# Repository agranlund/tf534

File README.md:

# TerribleFire   [![Badge License]][License]

*Atari Accelerator Card Firmware.*

<br>

## Supported Cards

<kbd>  TF530  </kbd>  <kbd>  TF534  </kbd>

<br>
<br>

## Note

By default the **TF534** doesn't work under  `25Mhz` .

With this firmware, it can work from  `25Mhz`  up to <br>
`50Mhz` , thou it is optimized for  `33Mhz`  &  `50Mhz` .

<br>
<br>

## BOM

*Where this* ***BOM*** *differs from the schematic use the* ***BOM*** *value.*

<br>

|       Part       |       Value       |         Device          |        Package         |            Description            |
|:----------------:|:-----------------:|:-----------------------:|:----------------------:|:---------------------------------:|
| `C1 - C15`       | `10uF`            | `CAP_1206_X7R`          | `1206`                 |  Ceramic Capacitors               |
| `C16 + C17`      | `0.1uF`           | `CAP_0603_X7R`          | `0603`                 | `CAP-00810`                       |
| `C18`            | `0.1uF`           | `CAP_1206_X7R`          | `1206`                 |  Ceramic Capacitors               |
| `C19`            | `0.1uF`           | `CAP_0603_X7R`          | `0603`                 |                                   |
| `C20`            | `0.1uF`           | `CAP_0603_X7R`          | `0603`                 | `CAP-00810`                       |
| `C21 - C30`      | `0.1uF`           | `CAP_0603_X7R`          | `0603`                 |                                   |
| `C31`            | `10uF`            | `CAP_1206_X7R`          | `1206`                 |  Ceramic Capacitors               |
| `IC1`            | `MC68030RC`       | `68030`                 | `MPGA128`              | `MOTOROLA`                        |
| `IC2`            | `MC68881FN-SOC`   | `68882`                 | `PLCC68-S`             | `unknown`                         |
| `IC3`            | `LM1117-3.3`      | `V_REG_LM1117SOT223`    | `SOT223`               | Voltage Regulator `LM1117`        |
| `IC4 - IC5`      | `74LVC1G17DBV`    | `74LVC1G17DBV`          | `SOT23-5`              |  Single Schmitt-Trigger Buffer    |
| `IC6 - IC9`      | `AS6C800855ZIN`   | `AS6C800855ZIN`         | `TSOP44-II`            |                                   |
| `IC10`           | `74AC16245`       | `74AC16245`             | `SSOP48DL`             | `16-bit` \| `3-state` \|BUS Transceiver |
| `IDECONNECTOR`   | `87758-4416`      | `87758-4416`            | `87758-4416`           | `44 Pin` \| `2mm` \| Dual Row HDR |
| `INT2`           | `PINHD-1X1`       | `1X01`                  | `PIN HEADER`           |                                   |
| `JP1`            | `CLOCKSEL`        | `JUMPER-3PTH`           | `1X03`                 |                                   |
| `JP2`            | `Z2ROM`           | `JUMPER-2PTH`           | `1X02`                 |  Jumper                           |
| `JP3`            | `MMUDIS`          | `JUMPER-2PTH`           | `1X02`                 |  Jumper                           |
| `JP4`            | `ROMEN`           | `JUMPER-2PTH`           | `1X02`                 |  Jumper                           |
| `JP5`            | `CDIS`            | `JUMPER-2PTH`           | `1X02`                 |  Jumper                           |
| `JTAG`           | `JTAG`            | `HEADER-1X6`            | `0.1 header x 6`       |  Pin Header                       |
| `OSCCPU`         | `CPUMHZ`          | `OSCILLATOR`            | `OSC_7X5MM`            |  Oscillators                      |
| `PWR1`           | `EXT5V`           | `JUMPER-2PTH`           | `1X02`                 |  Jumper                           |
| `R1 + R2`        | `2K2`             | `0.05OHM-1/5W-1%(0603)` | `0603`                 | `RES-12535`                       |
| `R3`             | `47K`             | `RESISTOR1206`          | `1206`                 |  Resistors                        |
| `RN1 - RN3`      | `CAY16-222J4LF`   | `CAY16-222J4LF`         | `RESCAXE80P320X160-8N` | Res Thick Film Array `2.2KΩ`      |
| `SPIPORT`        | `SPI PORT`        | `PINHD-2X6`             | `2X06`                 |  Pin Header                       |
| `SPI_INT`        | `NONE`            | `PINHD-1X1`             | `1X01`                 |  Pin Header                       |
| `U1`             | `3.3V SPI Flash`  | `SST26VF016B`           | `SO08`                 | `32M` Serial Flash Memory         |
| `X1`             | `MC68000`         | `MC68000P`              | `DIL64`                | `68xxx` Processor                 |
| `XC9572XL(BUS)`  | `XC9572XL-VQ64`   | `XC9572XL-VQ64`         | `VQ64`                 |                                   |
| `XC95144XL(RAM)` | `XC95144XL-TQ100` | `XC95144XL-TQ100`       | `TQFP100`              |                                   |

<br>

<!----------------------------------------------------------------------------->

[Badge License]: https://img.shields.io/badge/License-GPL2-015d93.svg?style=for-the-badge&labelColor=blue

[License]: LICENSE

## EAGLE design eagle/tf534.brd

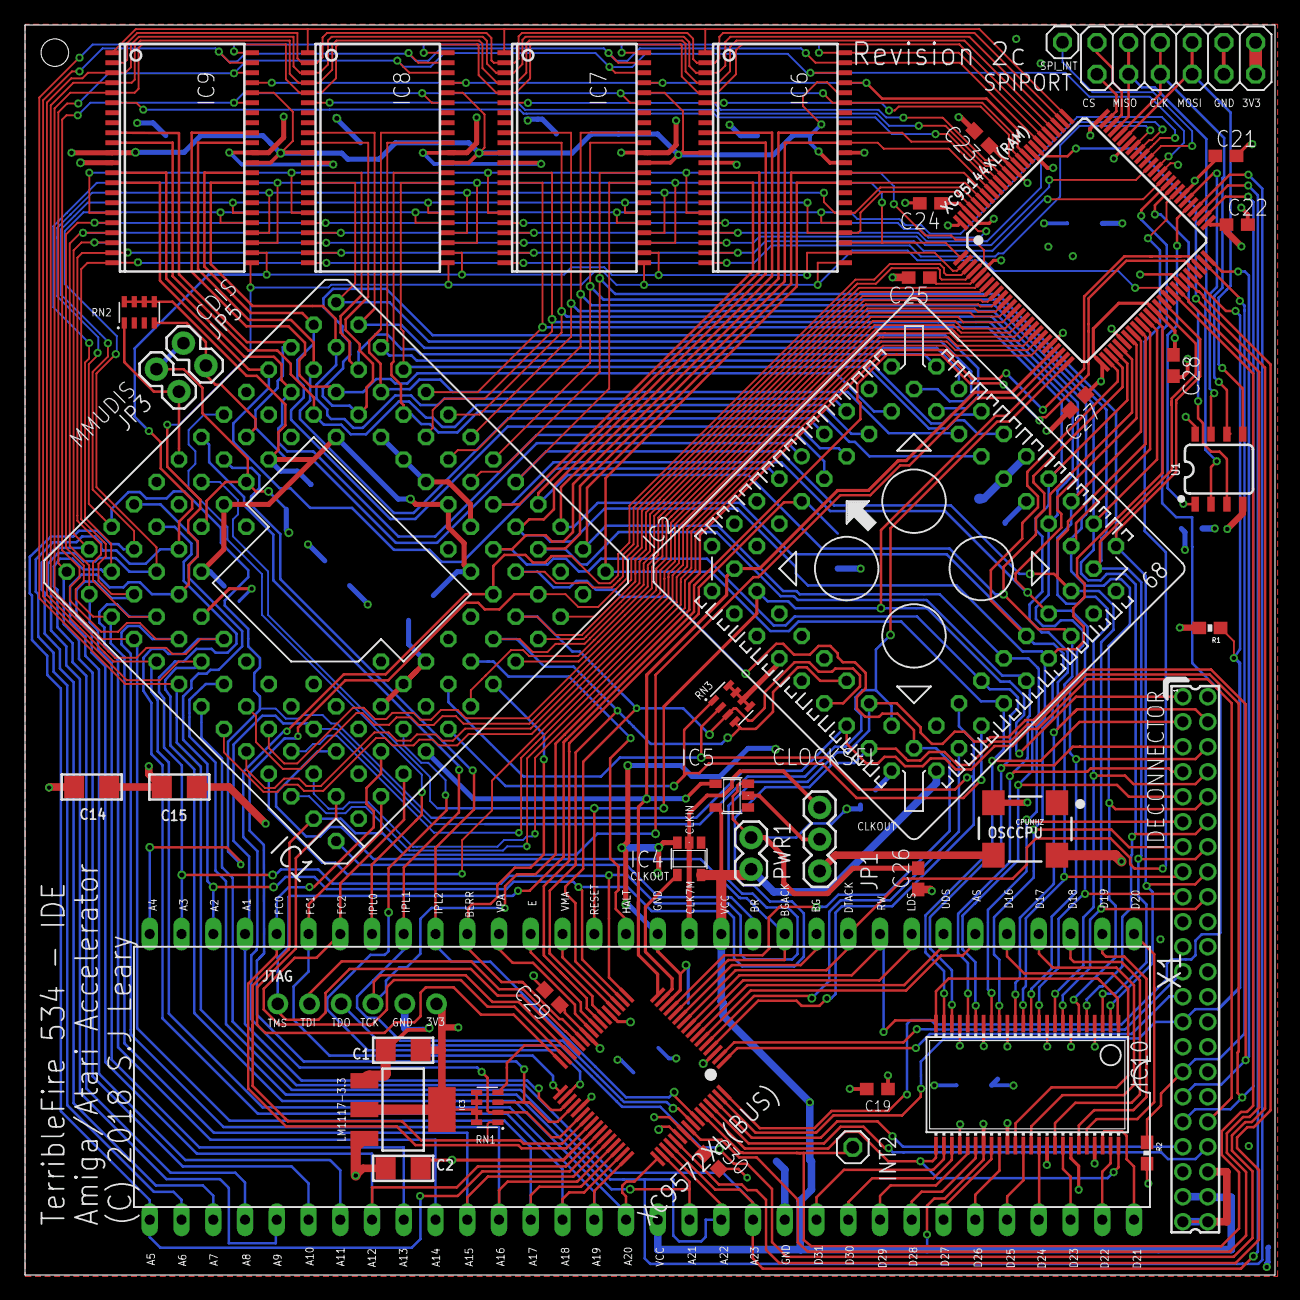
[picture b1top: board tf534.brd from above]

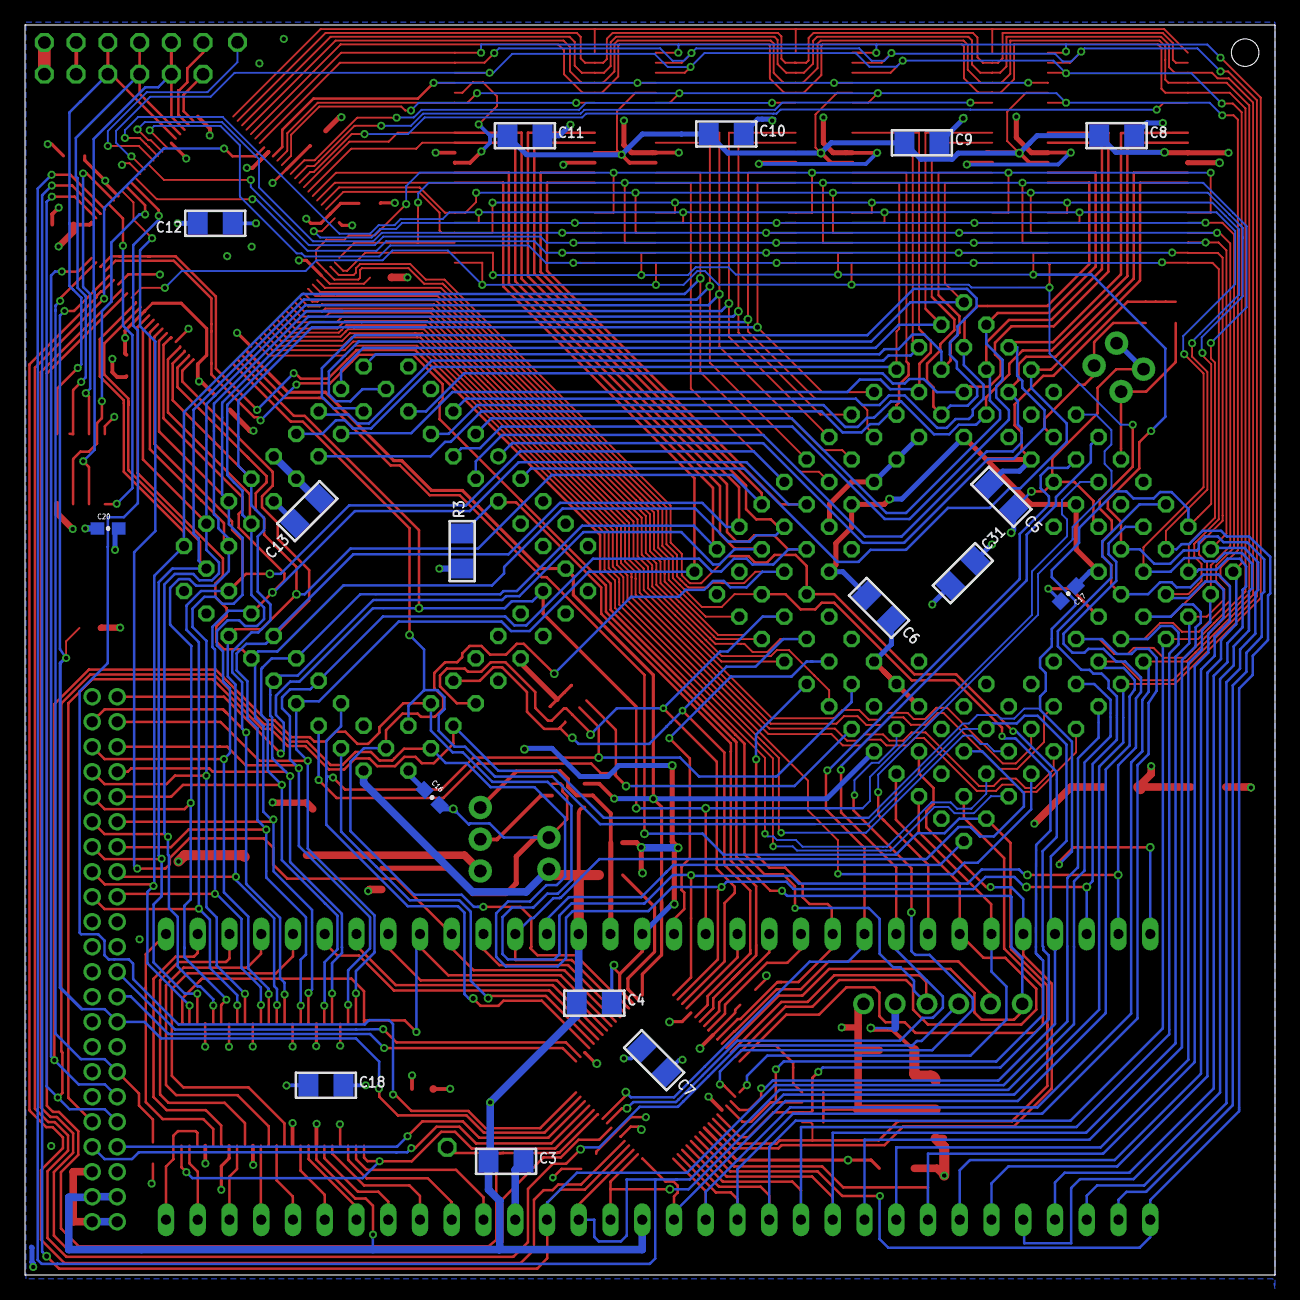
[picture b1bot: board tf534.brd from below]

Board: 4 copper layers, 100.0 x 100.0 mm, 61 parts (17 on the bottom side), 156 nets.

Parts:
C1, C2, C3, C4, C5, C6, C7, C8, C9, C10, C11, C12, C13, C14, C15, C31: 10uF; 1206
C16, C17, C20: 0.1uF; 0603-CAP
C18: 100nF; 1206
C19, C21, C22, C23, C24, C25, C26, C27, C28, C29, C30: C0603
IC1: MPGA128
IC2: PLCC68-S
IC3: LM1117-3.3; SOT223
IC4, IC5: 74LVC1G17DBV; SOT23-5
IC6, IC7, IC8, IC9: AS6C800855ZIN; TSOP44-II
IC10: 74AC16245; SSOP48DL
IDECONNECTOR: 87758-4416
INT2: 1X01
JP1: CLOCKSEL; 1X03
JP3: MMUDIS; 1X02
JP5: CDIS; 1X02
JTAG: JTAG; 1X06_ROUND
OSCCPU: CPUMHZ; OSC_7X5MM
PWR1: EXT5V; 1X02
R1, R2: 1K; 0603
R3: 47K; 1206
RN1, RN2, RN3: CAY16-103J4LF; RESCAXE80P320X160-8N
SPIPORT: SPI PORT; 2X06
SPI_INT: NONE; 1X01
U1: 3.3V SPI Flash; SO08
X1: MC68000; DIL64
XC9572XL(BUS): TERRIBLEFIRE_XC9572XL-VQ64; TERRIBLEFIRE_VQ64
XC95144XL(RAM): XC95144XL-TQ100; TQFP100

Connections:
A0: IC1.A02, RN1.1, XC9572XL(BUS).39, XC95144XL(RAM).23
A1: IC1.C04, IC2.25, X1.29, XC9572XL(BUS).35, XC95144XL(RAM).25
A2: IC1.D13, IC2.24, IDECONNECTOR.35, X1.30, XC9572XL(BUS).18, XC95144XL(RAM).52
A3: IC1.D12, IC2.23, IDECONNECTOR.33, X1.31, XC9572XL(BUS).17, XC95144XL(RAM).50
A4: IC1.C13, IC2.22, IC6.28, IC7.26, IC8.26, IC9.26, IDECONNECTOR.36, X1.32, XC95144XL(RAM).96
A5: IC1.C12, IC6.26, IC7.28, IC8.28, IC9.28, X1.33, XC9572XL(BUS).43, XC95144XL(RAM).97
A6: IC1.D11, IC6.24, IC7.24, IC8.24, IC9.24, X1.34, XC95144XL(RAM).2
A7: IC1.B13, IC6.20, IC7.20, IC8.20, IC9.20, X1.35, XC95144XL(RAM).64
A8: IC1.B12, IC6.25, IC7.25, IC8.25, IC9.25, X1.36, XC95144XL(RAM).1
A9: IC1.C11, IC6.27, IC7.27, IC8.27, IC9.27, X1.37, XC95144XL(RAM).66
A10: IC1.A13, IC6.42, IC7.42, IC8.42, IC9.42, X1.38, XC95144XL(RAM).63
A11: IC1.C10, IC6.23, IC7.23, IC8.23, IC9.23, X1.39, XC95144XL(RAM).41
A12: IC1.B11, IC6.22, IC7.22, IC8.22, IC9.22, X1.40, XC9572XL(BUS).42, XC95144XL(RAM).68
A13: IC1.A12, IC6.19, IC7.19, IC8.19, IC9.19, X1.41, XC95144XL(RAM).67
A14: IC1.B10, IC6.21, IC7.21, IC8.21, IC9.21, X1.42, XC95144XL(RAM).61
A15: IC1.A11, IC6.18, IC7.18, IC8.18, IC9.18, X1.43, XC9572XL(BUS).44, XC95144XL(RAM).99
A16: IC1.B09, IC6.39, IC7.39, IC8.39, IC9.39, X1.44, XC9572XL(BUS).45, XC95144XL(RAM).86
A17: IC1.A10, IC6.5, IC7.5, IC8.5, IC9.5, X1.45, XC9572XL(BUS).46, XC95144XL(RAM).80
A18: IC1.C08, IC6.4, IC7.4, IC8.4, IC9.4, X1.46, XC9572XL(BUS).47, XC95144XL(RAM).79
A19: IC1.A09, IC6.3, IC7.3, IC8.3, IC9.3, X1.47, XC9572XL(BUS).48, XC95144XL(RAM).78
A20: IC1.B08, IC6.43, IC7.43, IC8.43, IC9.43, X1.48, XC9572XL(BUS).49, XC95144XL(RAM).82
A21: IC1.A08, IC6.44, IC7.44, IC8.44, IC9.44, X1.50, XC9572XL(BUS).50, XC95144XL(RAM).81
A22: IC1.B07, X1.51, XC9572XL(BUS).51, XC95144XL(RAM).54
A23: IC1.A07, X1.52, XC9572XL(BUS).52, XC95144XL(RAM).53
A24: IC1.A06, XC95144XL(RAM).16
A25: IC1.B06, XC95144XL(RAM).14
A26: IC1.A05, XC95144XL(RAM).15
A27: IC1.B05, XC95144XL(RAM).13
A28: IC1.A04, XC95144XL(RAM).17
A29: IC1.B04, XC95144XL(RAM).18
A30: IC1.A03, XC95144XL(RAM).19
A31: IC1.B03, XC95144XL(RAM).20
AS: X1.6, XC9572XL(BUS).6
AS20: IC1.J02, IC2.21, RN3.4, XC9572XL(BUS).22, XC95144XL(RAM).10
AVEC: IC1.E02, XC9572XL(BUS).34
BERR: IC1.H01, X1.22, XC9572XL(BUS).27
BG: X1.11, XC9572XL(BUS).11
BG20: IC1.B02, RN1.4, XC9572XL(BUS).32
BGACK: IC1.C03, X1.12, XC9572XL(BUS).12
BR: IC1.A01, X1.13
BUSEN: IC10.25, IC10.48, XC9572XL(BUS).60
CBACK: IC1.J01, XC95144XL(RAM).12
CBREQ: IC1.K01, XC95144XL(RAM).9
CDIS: IC1.H12, JP5.2, RN2.4
CIIN: IC1.L01, XC95144XL(RAM).7
CLK7M: IC4.4, XC9572XL(BUS).15
CLK7M_RAW: IC4.2, JP1.1, X1.15
CLKCPU: IC1.E01, IC2.11, IC5.4, XC9572XL(BUS).16, XC95144XL(RAM).22
CLKCPU_RAW: IC5.2, JP1.2
CLKEXT: JP1.3, OSCCPU.3
CPCS: IC2.29, XC9572XL(BUS).5
CPSENSE: IC2.4, R3.2, XC9572XL(BUS).23
D0: IC1.K13, IC2.3, IC9.14
D1: IC1.K12, IC2.2, IC9.13
D2: IC1.L13, IC2.1, IC9.9
D3: IC1.M13, IC2.68, IC9.32
D4: IC1.L12, IC2.67, IC9.35
D5: IC1.K11, IC2.66, IC9.10
D6: IC1.M12, IC2.65, IC9.31
D7: IC1.L11, IC2.64, IC9.36
D8: IC1.N13, IC2.62, IC8.14
D9: IC1.M11, IC2.60, IC8.13
D10: IC1.L10, IC2.59, IC8.10
D11: IC1.N12, IC2.58, IC8.9
D12: IC1.M10, IC2.57, IC8.36
D13: IC1.N11, IC2.56, IC8.35
D14: IC1.M09, IC2.55, IC8.32
D15: IC1.N10, IC2.54, IC8.31
D16: IC1.N09, IC2.50, IC7.14, IC10.14, IDECONNECTOR.4, XC95144XL(RAM).29
D17: IC1.M08, IC2.49, IC7.13, IC10.12, IDECONNECTOR.6, XC95144XL(RAM).30
D18: IC1.N08, IC2.48, IC7.10, IC10.9, IDECONNECTOR.8, XC95144XL(RAM).33
D19: IC1.N07, IC2.47, IC7.9, IC10.6, IDECONNECTOR.10, XC95144XL(RAM).35
D20: IC1.M07, IC2.46, IC7.36, IC10.5, IDECONNECTOR.12, XC95144XL(RAM).36
D21: IC1.N06, IC2.45, IC7.35, IC10.3, IDECONNECTOR.14, XC95144XL(RAM).39
D22: IC1.M06, IC2.44, IC7.32, IC10.2, IDECONNECTOR.16, XC95144XL(RAM).40
D23: IC1.N05, IC2.42, IC7.31, IC10.8, IDECONNECTOR.18, XC95144XL(RAM).34
D24: IC1.M05, IC2.40, IC6.14, IC10.11, IDECONNECTOR.17, XC95144XL(RAM).32
D25: IC1.N04, IC2.39, IC6.13, IC10.13, IDECONNECTOR.15, XC95144XL(RAM).28
D26: IC1.N03, IC2.38, IC6.9, IC10.16, IDECONNECTOR.13, XC95144XL(RAM).27
D27: IC1.M04, IC2.37, IC6.10, IC10.17, IDECONNECTOR.11, XC95144XL(RAM).37
D28: IC1.N02, IC2.36, IC6.32, IC10.19, IDECONNECTOR.9, XC95144XL(RAM).94
D29: IC1.M03, IC2.35, IC6.35, IC10.20, IDECONNECTOR.7, XC95144XL(RAM).93
D30: IC1.L04, IC2.34, IC6.36, IC10.22, IDECONNECTOR.5, XC95144XL(RAM).92
D31: IC1.N01, IC2.33, IC6.31, IC10.23, IDECONNECTOR.3, XC95144XL(RAM).95
D68K0: IC10.35, X1.5
D68K1: IC10.37, X1.4
D68K2: IC10.40, X1.3
D68K3: IC10.43, X1.2
D68K4: IC10.44, X1.1
D68K5: IC10.46, X1.64
D68K6: IC10.47, X1.63
D68K7: IC10.41, X1.62
D68K8: IC10.38, X1.61
D68K9: IC10.36, X1.60
D68K10: IC10.33, X1.59
D68K11: IC10.32, X1.58
D68K12: IC10.30, X1.57
D68K13: IC10.29, X1.56
D68K14: IC10.27, X1.55
D68K15: IC10.26, X1.54
DS20: IC1.K02, IC2.20, RN3.3, XC9572XL(BUS).19, XC95144XL(RAM).8
DSACK0: IC1.F01, IC2.31, RN3.1
DSACK1: IC1.G02, IC2.32, RN3.2, XC9572XL(BUS).4
DTACK: X1.10, XC9572XL(BUS).10, XC95144XL(RAM).58
E: X1.20, XC9572XL(BUS).24
FC0: IC1.D02, X1.28, XC9572XL(BUS).40
FC1: IC1.C01, X1.27, XC9572XL(BUS).33
FC2: IC1.D01, X1.26, XC9572XL(BUS).31
GND: C1.2, C2.2, C3.2, C4.2, C5.2, C6.2, C7.2, C8.2, C9.2, C10.2, C11.2, C12.2, C13.2, C14.2, C15.2, C16.2, C17.2, C18.2, C19.2, C20.2, C21.2, C22.2, C23.2, C24.2, C25.2, C26.2, C27.2, C28.2, C29.2, C30.2, C31.2, IC1.C05, IC1.C07, IC1.C09, IC1.E03, IC1.E11, IC1.F03, IC1.G03, IC1.G11, IC1.J03, IC1.J11, IC1.L05, IC1.L07, IC1.L08, IC1.L09, IC2.5, IC2.6, IC2.7, IC2.8, IC2.9, IC2.12, IC2.14, IC2.19, IC2.30, IC2.41, IC2.51, IC2.63, IC3.1, IC4.3, IC5.3, IC6.12, IC6.34, IC7.12, IC7.34, IC8.12, IC8.34, IC9.12, IC9.34, IC10.4, IC10.10, IC10.15, IC10.21, IC10.28, IC10.34, IC10.39, IC10.45, IDECONNECTOR.2, IDECONNECTOR.19, IDECONNECTOR.22, IDECONNECTOR.24, IDECONNECTOR.26, IDECONNECTOR.30, IDECONNECTOR.40, IDECONNECTOR.43, IDECONNECTOR.44, JP3.1, JP5.1, JTAG.5, OSCCPU.2, PWR1.1, R2.2, SPIPORT.3, SPIPORT.4, U1.4, X1.16, X1.53, XC9572XL(BUS).14, XC9572XL(BUS).21, XC9572XL(BUS).41, XC9572XL(BUS).54, XC95144XL(RAM).21, XC95144XL(RAM).31, XC95144XL(RAM).44, XC95144XL(RAM).62, XC95144XL(RAM).69, XC95144XL(RAM).75, XC95144XL(RAM).84, XC95144XL(RAM).100
HALT: IC1.H02, X1.17
HOLD: U1.7, XC95144XL(RAM).56
IDECS0: IDECONNECTOR.37, XC9572XL(BUS).62
IDECS1: IDECONNECTOR.38, XC9572XL(BUS).61
IDEINT: IDECONNECTOR.31, R2.1, XC95144XL(RAM).49
IDEWAIT: IDECONNECTOR.27, R1.1, XC9572XL(BUS).63, XC95144XL(RAM).46
INT2: INT2.1, XC9572XL(BUS).59, XC95144XL(RAM).42
INTCYCLE: XC9572XL(BUS).56, XC95144XL(RAM).43
IOR: IDECONNECTOR.25, XC9572XL(BUS).1
IOW: IDECONNECTOR.23, XC9572XL(BUS).2
IPL0: IC1.H13, X1.25
IPL1: IC1.G13, X1.24, XC9572XL(BUS).57
IPL2: IC1.G12, X1.23, XC9572XL(BUS).58
LDS: X1.8, XC9572XL(BUS).8
MMUDIS: IC1.F13, JP3.2, RN2.1
R/W: IC10.1, IC10.24, X1.9, XC9572XL(BUS).9
R/W20: IC1.L03, IC2.28, IC6.17, IC7.17, IC8.17, IC9.17, XC9572XL(BUS).13, XC95144XL(RAM).4
RAMA2: IC6.1, IC7.1, IC8.1, IC9.1, XC95144XL(RAM).76
RAMA3: IC6.2, IC7.2, IC8.2, IC9.2, XC95144XL(RAM).77
RAMCS0: IC9.6, XC95144XL(RAM).91
RAMCS1: IC8.6, XC95144XL(RAM).90
RAMCS2: IC7.6, XC95144XL(RAM).89
RAMCS3: IC6.6, XC95144XL(RAM).87
RAMOE: IC6.41, IC7.41, IC8.41, IC9.41, XC95144XL(RAM).85
RESET: IC1.F12, IC2.13, IDECONNECTOR.1, X1.18, XC95144XL(RAM).24
SIZ0: IC1.L02, RN1.3, XC9572XL(BUS).36, XC95144XL(RAM).6
SIZ1: IC1.K03, RN1.2, XC9572XL(BUS).38, XC95144XL(RAM).3
SPARE: XC9572XL(BUS).64, XC95144XL(RAM).60
SPI_CLK: SPIPORT.7, SPIPORT.8, U1.6, XC95144XL(RAM).71
SPI_CS0: SPIPORT.11, XC95144XL(RAM).73
SPI_CS1: SPIPORT.12, XC95144XL(RAM).74
SPI_CS2: U1.1, XC95144XL(RAM).55
SPI_INT: SPI_INT.1, XC95144XL(RAM).65
SPI_MISO: SPIPORT.9, SPIPORT.10, U1.2, XC95144XL(RAM).72
SPI_MOSI: SPIPORT.5, SPIPORT.6, U1.5, XC95144XL(RAM).70
STERM: IC1.G01, XC95144XL(RAM).11
TCK: JTAG.4, XC9572XL(BUS).30, XC95144XL(RAM).48
TDI: JTAG.2, XC9572XL(BUS).28
TDINT: XC9572XL(BUS).53, XC95144XL(RAM).45
TDO: JTAG.3, XC95144XL(RAM).83
TMS: JTAG.1, XC9572XL(BUS).29, XC95144XL(RAM).47
UDS: X1.7, XC9572XL(BUS).7
VCC: C2.1, C3.1, C4.1, C5.1, C6.1, C8.1, C9.1, C10.1, C11.1, C13.1, C14.1, C15.1, C16.1, C17.1, C18.1, C19.1, C31.1, IC1.C06, IC1.D04, IC1.D10, IC1.F02, IC1.F11, IC1.H03, IC1.H11, IC1.K04, IC1.K10, IC1.L06, IC2.10, IC2.16, IC2.17, IC2.18, IC2.26, IC2.27, IC2.43, IC2.52, IC2.53, IC2.61, IC3.3, IC4.5, IC5.5, IC6.11, IC6.33, IC6.40, IC7.11, IC7.33, IC7.40, IC8.11, IC8.33, IC8.40, IC9.11, IC9.33, IC9.40, IC10.7, IC10.18, IC10.31, IC10.42, IDECONNECTOR.41, IDECONNECTOR.42, PWR1.2, R3.1, RN2.5, RN2.6, RN2.7, RN2.8, RN3.5, RN3.6, RN3.7, RN3.8, X1.14, X1.49
VCC33: C1.1, C7.1, C12.1, C20.1, C21.1, C22.1, C23.1, C24.1, C25.1, C26.1, C27.1, C28.1, C29.1, C30.1, IC3.2, IC3.4, JTAG.6, OSCCPU.4, R1.2, RN1.5, RN1.6, RN1.7, RN1.8, SPIPORT.1, SPIPORT.2, U1.8, XC9572XL(BUS).3, XC9572XL(BUS).26, XC9572XL(BUS).37, XC9572XL(BUS).55, XC95144XL(RAM).5, XC95144XL(RAM).26, XC95144XL(RAM).38, XC95144XL(RAM).51, XC95144XL(RAM).57, XC95144XL(RAM).88, XC95144XL(RAM).98
VMA: X1.19, XC9572XL(BUS).20
VPA: X1.21, XC9572XL(BUS).25
WRITEPROT: U1.3, XC95144XL(RAM).59

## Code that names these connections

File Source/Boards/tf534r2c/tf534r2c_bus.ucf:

# Copyright (C) 2016-2019, Stephen J. Leary
# All rights reserved.
# 
# This file is part of  TF534 (Terrible Fire 030 Accelerator).
# 
# This program is free software; you can redistribute it and/or
# modify it under the terms of the GNU General Public License
# as published by the Free Software Foundation; version 2 only.
# 
# This program is distributed in the hope that it will be useful,
# but WITHOUT ANY WARRANTY; without even the implied warranty of
# MERCHANTABILITY or FITNESS FOR A PARTICULAR PURPOSE.  See the
# GNU General Public License for more details.
# 
# You should have received a copy of the GNU General Public License
# along with this program; if not, write to the Free Software
# Foundation, Inc., 51 Franklin Street, Fifth Floor, Boston, MA  02110-1301, USA.
#

#Clocks
NET "CLKCPU"		LOC="16";
NET "CLKCPU" BUFG=CLK;
NET "CLKCPU" TNM_NET = "CLKCPU"; # gives the net clk a group name as CLKCPU
TIMESPEC "TS_CLKCPU" = PERIOD "CLKCPU" 20 ns ; # add 20 ns PERIOD constraint the
OFFSET = IN 15 ns VALID 10 ns BEFORE "CLKCPU" ; # add  offset in constraint
OFFSET = OUT 15 ns AFTER "CLKCPU" ; # add  offset out constraint
NET "CLK7M"		LOC="15";
NET "CLK7M" BUFG=CLK;
NET "CLK7M" TNM_NET = "CLK7M"; # gives the net clk a group name as CLK7M
TIMESPEC "TS_CLK7M" = PERIOD "CLK7M" 139 ns ; # add 139 ns PERIOD constraint the
#Created by Constraints Editor (xc9572xl-vq64-10) - 2018/04/08
OFFSET = IN 20 ns VALID 10 ns BEFORE "CLK7M"; # add  offset in constraint
OFFSET = OUT 15 ns AFTER "CLK7M" ; # add  offset out constraint
NET "A<0>"      LOC="39";
NET "A<1>"      LOC="35";
NET "A<2>"      LOC="18";
NET "A<3>"      LOC="17";
NET "A<5>"      LOC="43";
NET "A<12>"      LOC="42";
NET "A<15>"      LOC="44";
NET "A<16>"      LOC="45";
NET "A<17>"      LOC="46";
NET "A<18>"      LOC="47";
NET "A<19>"      LOC="48";
NET "A<20>"      LOC="49";
NET "A<21>"      LOC="50";
NET "A<22>"      LOC="51";
NET "A<23>"      LOC="52";
NET "AS"      LOC="6";
NET "AS20"      LOC="22";
NET "AVEC"      LOC="34";
NET "BERR"      LOC="27";
NET "BG"      LOC="11";
NET "BG20"      LOC="32";
NET "BGACK"      LOC="12";
NET "BUSEN"      LOC="60";
NET "CPCS"      LOC="5";
NET "CPSENSE"      LOC="23";
NET "DS20"      LOC="19";
NET "DSACK1"      LOC="4";
NET "DTACK"      LOC="10";
NET "E"      LOC="24";
NET "FC<0>"      LOC="40";
NET "FC<1>"      LOC="33";
NET "FC<2>"      LOC="31";
NET "IDECS<0>"      LOC="62";
NET "IDECS<1>"      LOC="61";
NET "IDEWAIT"      LOC="63";
NET "INT2"      LOC="59";
NET "INTCYCLE"      LOC="56";
NET "IOR"      LOC="1";
NET "IOW"      LOC="2";
NET "IPL<1>"      LOC="57";
NET "IPL<2>"      LOC="58";
NET "LDS"      LOC="8";
NET "RW"      LOC="9";
NET "RW20"      LOC="13";
NET "SIZ<0>"      LOC="36";
NET "SIZ<1>"      LOC="38";
NET "SLOWCYCLE"      LOC="64";
NET "UDS"      LOC="7";
NET "VMA"      LOC="20";
NET "VPA"      LOC="25";

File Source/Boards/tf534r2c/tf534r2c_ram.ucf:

# Copyright (C) 2016-2019, Stephen J. Leary
# All rights reserved.
# 
# This file is part of  TF534 (Terrible Fire 030 Accelerator).
# 
# This program is free software; you can redistribute it and/or
# modify it under the terms of the GNU General Public License
# as published by the Free Software Foundation; version 2 only.
# 
# This program is distributed in the hope that it will be useful,
# but WITHOUT ANY WARRANTY; without even the implied warranty of
# MERCHANTABILITY or FITNESS FOR A PARTICULAR PURPOSE.  See the
# GNU General Public License for more details.
# 
# You should have received a copy of the GNU General Public License
# along with this program; if not, write to the Free Software
# Foundation, Inc., 51 Franklin Street, Fifth Floor, Boston, MA  02110-1301, USA.
#

#Clocks
NET "CLKCPU"      LOC="22";
NET "CLKCPU" BUFG=CLK;
NET "CLKCPU" TNM_NET = "CLKCPU"; # gives the net clk a group name as CLKCPU
TIMESPEC "TS_CLKCPU" = PERIOD "CLKCPU" 12 ns ; # add 20 ns PERIOD constraint the
#OFFSET = IN 15 ns VALID 5ns BEFORE "CLKCPU" ; # add  offset in constraint
OFFSET = OUT 5 ns AFTER "CLKCPU" ; # add  offset out constraint

NET "A<0>"       LOC="23";
NET "A<1>"       LOC="25";
NET "A<2>"       LOC="52";
NET "A<3>"       LOC="50";
NET "A<4>"       LOC="96";
NET "A<5>"       LOC="97";
NET "A<6>"       LOC="2";
NET "A<8>"       LOC="1";
NET "A<12>"      LOC="68";
NET "A<13>"      LOC="67";
NET "A<15>"      LOC="99";
NET "A<16>"      LOC="86";
NET "A<17>"      LOC="80";
NET "A<18>"      LOC="79";
NET "A<19>"      LOC="78";
NET "A<20>"      LOC="82";
NET "A<21>"      LOC="81";
NET "A<22>"      LOC="54";
NET "A<23>"      LOC="53";
NET "A<24>"      LOC="16";
NET "A<25>"      LOC="14";
NET "A<26>"      LOC="15";
NET "A<27>"      LOC="13";
NET "A<28>"      LOC="17";
NET "A<29>"      LOC="18";
NET "A<30>"      LOC="19";
NET "A<31>"      LOC="20";
NET "AS20"       LOC="10";
NET "CBACK"      LOC="12";
NET "CBREQ"      LOC="9";
NET "CIIN"       LOC="7";

NET "D<0>"       LOC="29";
NET "D<1>"       LOC="30";
NET "D<2>"       LOC="33";
NET "D<3>"       LOC="35";
NET "D<4>"       LOC="36";
NET "D<5>"       LOC="39";
NET "D<6>"       LOC="40";
NET "D<7>"       LOC="34";
NET "D<8>"       LOC="32";
NET "D<9>"       LOC="28";
NET "D<10>"      LOC="27";
NET "D<11>"      LOC="37";
NET "D<12>"      LOC="94";
NET "D<13>"      LOC="93";
NET "D<14>"      LOC="92";
NET "D<15>"      LOC="95";

NET "DS20"       LOC="8";
NET "DTACK"      LOC="58";
NET "HOLD"       LOC="56";
NET "IDEINT"     LOC="49";
NET "IDEWAIT"    LOC="46";
NET "INT2"       LOC="42";
NET "INTCYCLE"   LOC="43";
NET "RW20"       LOC="4";
NET "RAMA<2>"    LOC="76";
NET "RAMA<3>"    LOC="77";
NET "RAMCS<0>"   LOC="91";
NET "RAMCS<1>"   LOC="90";
NET "RAMCS<2>"   LOC="89";
NET "RAMCS<3>"   LOC="87";
NET "RAMOE"      LOC="85";
NET "RESET"      LOC="24";
#NET "ROMEN<0>"  LOC="66";
#NET "ROMEN<1>"  LOC="64";
NET "SIZ<0>"     LOC="6";
NET "SIZ<1>"     LOC="3";
NET "SLOWCYCLE"  LOC="60";
NET "SPI_CLK"    LOC="71";
NET "SPI_CS<0>"  LOC="73";
NET "SPI_CS<1>"  LOC="74";
NET "SPI_WCS"    LOC="55";
#NET "SPI_INT"   LOC="65";
NET "SPI_MISO"   LOC="72";
NET "SPI_MOSI"   LOC="70";
NET "STERM"      LOC="11";
NET "WRITEPROT"  LOC="59";

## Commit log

2019-03-28 added the open board view file
2019-03-28 wrong license.
2019-06-09 Adding all the sources for the TF534 and TF53x firmwares
2019-09-25 Added Atari support to TF534r2c
    - Exposed onboard ram as TT-RAM
    - IDE interface mapped for Atari
    - IDE interrupt wired to INT2 pin (connect to ASCI10 for IDE support under Atari TOS)
2019-10-22 Atari TF530r3
    TF530r3:
    - Makefile fixes to allow building this board for Atari
    - Expose onboard ram as 2MB TT-RAM at 0x01000000
2019-10-27 Fixed blitter access on Atari
    Changed bus delay to make Blitter happy
2019-10-27 Binaries in /bin folder
2021-12-20 Adjusted README
2022-07-05 Updated Formatting
2022-07-05 Sorted Files
2022-07-05 Fixed Makefile Paths
2022-07-05 Ignore Build Files
2022-07-05 Sorted File
2022-08-02 Adjusted Badge Style

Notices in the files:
eagle/tf534.brd:
(C) 2018 S.J Leary
parts and their libraries:
microbuilder: This work is placed in the public domain, and may be freely used for commercial and non-commercial work with the following conditions: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
SparkFun-Retired: Licensing:Creative Commons ShareAlike 4.0 International - https://creativecommons.org/licenses/by-sa/4.0
